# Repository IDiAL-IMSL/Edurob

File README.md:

# EduRobV2
[Homepage](https://www.imsl.fh-dortmund.de/mobile-roboter/edurob/)
## Educational robot with support for various drive kinematics

EduRob is a handy mobile robot specially designed for education. Through clever design, it is possible to cover different types of drives such as Mecanum, Omniwheel, and differential drive.

## Detailed information:

[Getting Started](Doc/README.md)

[Partslist](Doc/Partslist/README.md)

[PCB](https://github.com/IDiAL-IMSL/Edurob-PCB)

[CAD](https://github.com/IDiAL-IMSL/Edurob-CAD/README.md)

## Example projects:

[SLAM](Projects/SLAM/README.md)

[Line Follower](https://github.com/blssed/EduRob-LineFollower)

---

## Background

In the robotics lab, there is a wide range of different robots available for use in teaching and for the completion of thesis projects. However, they all share one major disadvantage: they prefer to drive themselves rather than being carried. As a result, their application is limited to the lab itself and adjacent rooms.

Especially for basic training in mobile robotics such as controlling different types of drives (Mecanum, Omniwheel, or differential drive), implementing control tasks, and connecting sensors, the experimental area of the robotics lab is not necessarily required. This led to the requirement of developing a flexible platform that can cover all types of drives, and small enough to be taken in a backpack to the home office.

# Possible configurations

EduRob can be equipped with three or four motors and different types of wheels. The motors can be flexibly reconnected by loosening two screws, and other wheels can be attached to the motor shaft.

## Mecanum 

With four motors at the four outer corners, EduRob can be turned into a robot with a classic Mecanum drive. The driving behavior is thus similar to that of OmniMan and the other Mecanum robots of the IMSL.

## Omniwheel with three wheels (120°)

With three motors, EduRob can simulate the classic omniwheel configuration. Three wheels rotated by 120° each allow for omnidirectional driving behavior.

## Omniwheel with four wheels (90°)

In addition to the classic arrangement with three omniwheels, EduRob can also simulate the special form with four omniwheels. Here, four omniwheels are arranged with a rotation of 90° to each other. In comparison to the Mecanum arrangement, the wheels are rotated by about 45°. In this configuration, EduRob can also be driven omnidirectionally.

## Differential drive or Skid-Steer drive

The driving behavior of the Pioneer robots in the IMSL inventory is made possible by the use of four wheels. Even though the arrangement of the wheels is similar to the Mecanum arrangement, sideways movement is not possible due to the use of classic wheels without freewheeling rollers. In addition to forward and backward movement and rotation around the center of the platform, driving in circular arcs is possible. This type of drive is also called Skid-Steer drive. Due to the 4x4 drive, this configuration is particularly suitable for rough terrain. The absence of freewheeling rollers on the wheels also means they are less likely to become contaminated or blocked.

By using two classic wheels and one or two non-driven Omniwheels, a proper differential drive is also possible. In this case, the rotation point moves to the midpoint between the two driven wheels. While this affects the robot's turning behavior (the front part swings out), it still maintains its limited range of movement (forward, backward, turning, and driving in circles). However, the "off-road" capability is reduced by the reduction to two driven wheels, and the use of Omniwheels increases the risk of contamination of free-rolling rollers.

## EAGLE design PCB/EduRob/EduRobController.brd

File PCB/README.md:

# EduRobController
[Homepage](https://www.imsl.fh-dortmund.de/mobile-roboter/edurob/)
## EduRob PCB

---

|No.| Device | URL |
|:---:|:---:|:---:|
| 1 |ESP32-PICO-KIT| [Link](https://docs.espressif.com/projects/esp-idf/en/latest/esp32/hw-reference/esp32/get-started-pico-kit.html)  |
| 2 | Dual DC Motordriver TB6612FNG (1A)  | [Link](https://www.sparkfun.com/products/14451)  |
| 3 | Motor 3 connector  | [Link](https://www.reichelt.de/jst-stiftleiste-rm-2-5-mm-1x6-polig-gerade-eh-jst-eh6p-st-p190551.html?search=JST+EH6P+ST+JST)  |
| 4 | Motor 1 connector  | [Link](https://www.reichelt.de/jst-stiftleiste-rm-2-5-mm-1x6-polig-gerade-eh-jst-eh6p-st-p190551.html?search=JST+EH6P+ST+JST)    |
| 5 | Supply Voltage Connector (max. 5VDC)  | -  |
| 6 | 5x20 Fuse (4A)  | -  |
| 7 | Supply Voltage Indicator  | -  |
| 8 | USB Voltage Indicator  | -  |
| 9 | Motor Enable Indicator  | -  |
| 10 | Logic Voltage Indicator  | -  |
| 11 | GPIO Header  | -  |
| 12 | Motor 0 connector  | [Link](https://www.reichelt.de/jst-stiftleiste-rm-2-5-mm-1x6-polig-gerade-eh-jst-eh6p-st-p190551.html?search=JST+EH6P+ST+JST)    |
| 13 | Motor 2 connector  | [Link](https://www.reichelt.de/jst-stiftleiste-rm-2-5-mm-1x6-polig-gerade-eh-jst-eh6p-st-p190551.html?search=JST+EH6P+ST+JST)    |
| 14 | Reset Button  | -    |

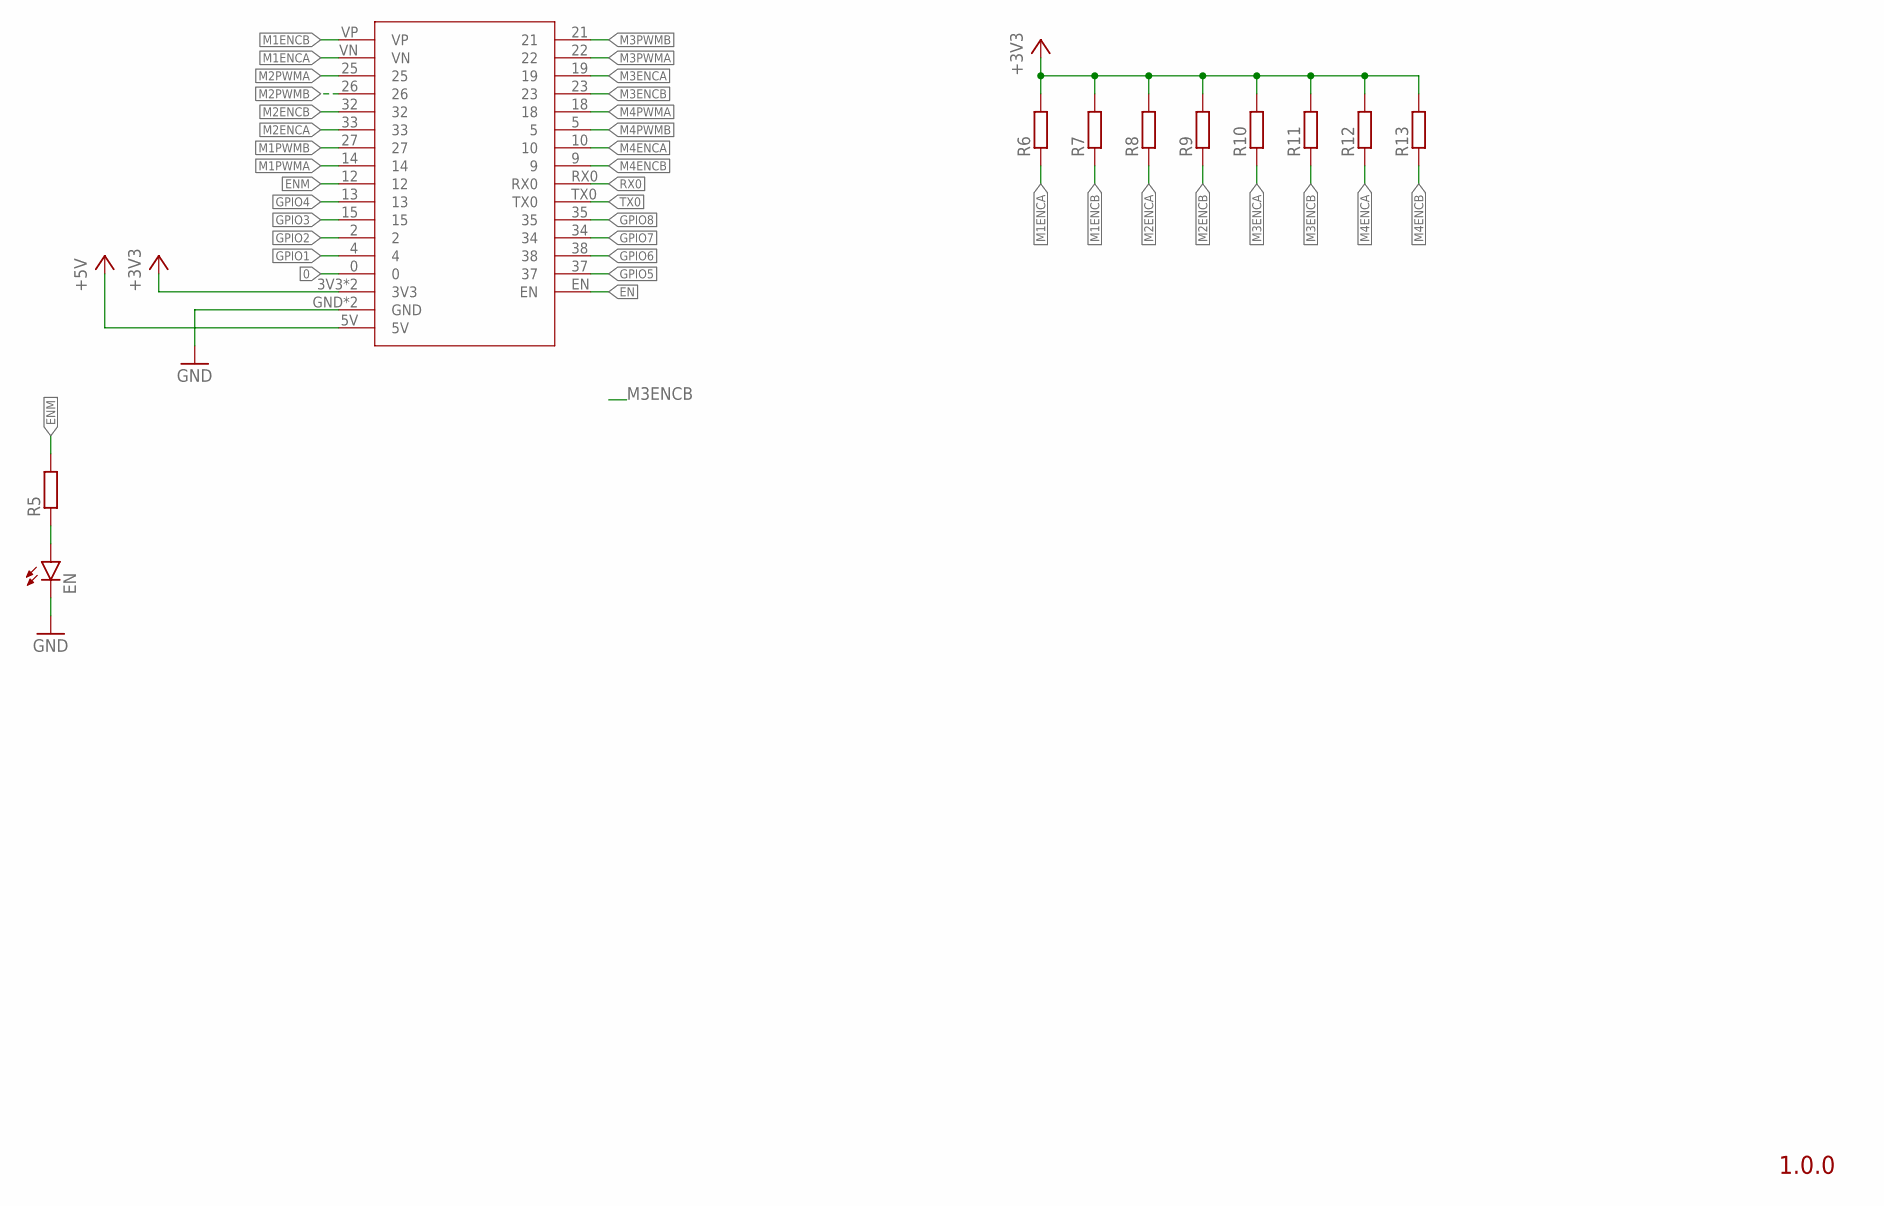
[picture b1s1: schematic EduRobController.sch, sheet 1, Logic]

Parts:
EN: LEDCHIP-LED0805; CHIP-LED0805
R5: R-EU_R0805; R0805
R6, R7, R8, R9, R10, R11, R12, R13: R-EU_R0603; R0603
U$1: ESP32

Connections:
0: U$1.0
+3V3: R6.2, R7.2, R8.2, R9.2, R10.2, R11.2, R12.2, R13.2, U$1.3V3, U$1.3V3. (3V3); also elsewhere on the board
+5V: U$1.5V; also elsewhere on the board
EN: U$1.EN; also elsewhere on the board
ENM: R5.2, U$1.12; also elsewhere on the board
GND: EN.C, U$1.GND, U$1.GND. (GND); also elsewhere on the board
GPIO1: U$1.4; also elsewhere on the board
GPIO2: U$1.2; also elsewhere on the board
GPIO3: U$1.15; also elsewhere on the board
GPIO4: U$1.13; also elsewhere on the board
GPIO5: U$1.37; also elsewhere on the board
GPIO6: U$1.38; also elsewhere on the board
GPIO7: U$1.34; also elsewhere on the board
GPIO8: U$1.35; also elsewhere on the board
M1ENCA: R6.1, U$1.VN; also elsewhere on the board
M1ENCB: R7.1, U$1.VP; also elsewhere on the board
M1PWMA: U$1.14; also elsewhere on the board
M1PWMB: U$1.27; also elsewhere on the board
M2ENCA: R8.1, U$1.33; also elsewhere on the board
M2ENCB: R9.1, U$1.32; also elsewhere on the board
M2PWMA: U$1.25; also elsewhere on the board
M2PWMB: U$1.26; also elsewhere on the board
M3ENCA: R10.1, U$1.19; also elsewhere on the board
M3ENCB: R11.1, U$1.23; also elsewhere on the board
M3PWMA: U$1.22; also elsewhere on the board
M3PWMB: U$1.21; also elsewhere on the board
M4ENCA: R12.1, U$1.10; also elsewhere on the board
M4ENCB: R13.1, U$1.9; also elsewhere on the board
M4PWMA: U$1.18; also elsewhere on the board
M4PWMB: U$1.5; also elsewhere on the board
unnamed: EN.A, R5.1
RX0: U$1.RX0
TX0: U$1.TX0

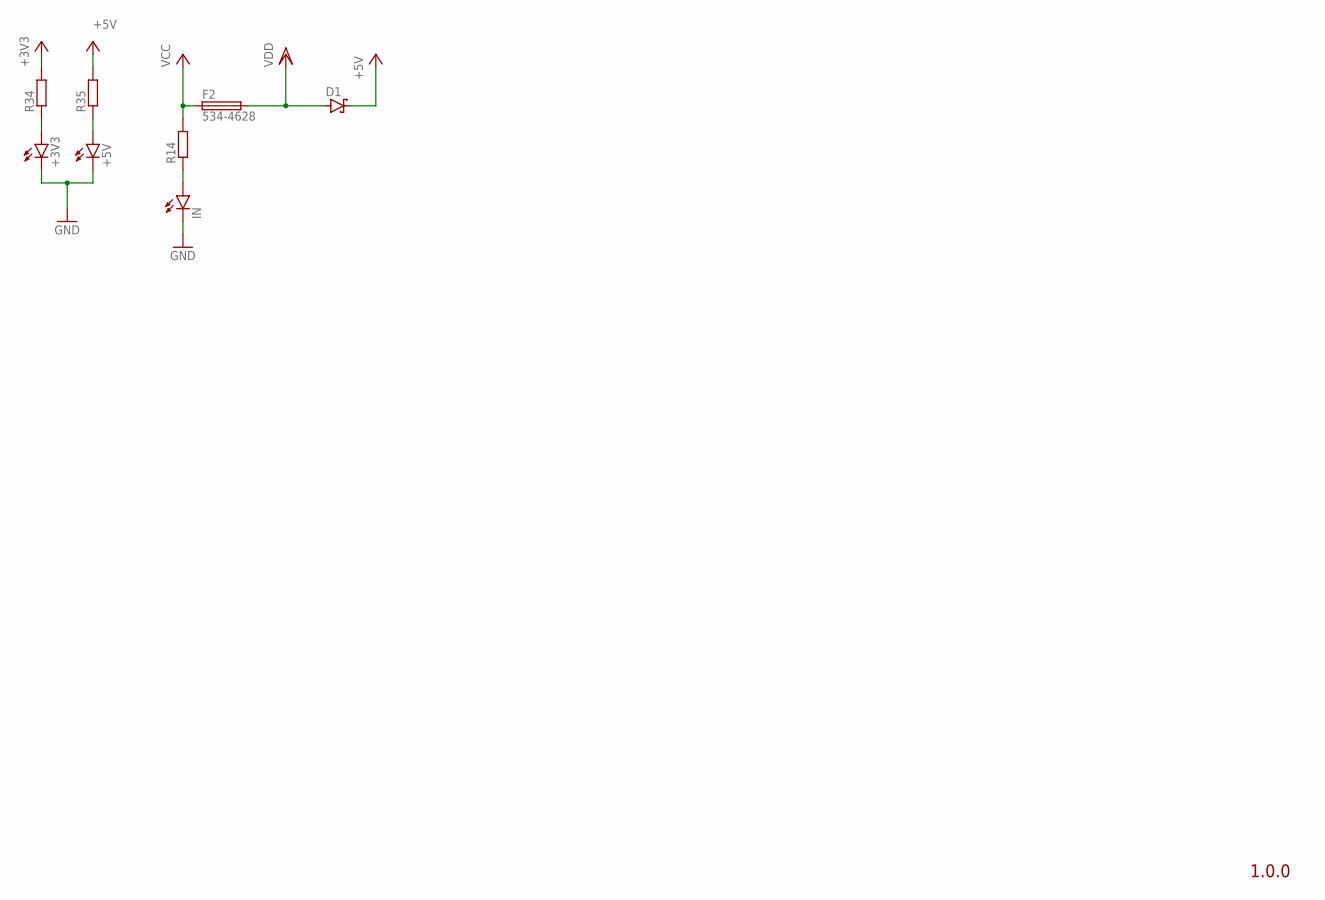
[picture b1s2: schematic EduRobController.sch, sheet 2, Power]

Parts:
+3V3, +5V: LEDCHIP-LED0805; CHIP-LED0805
D1: SCHOTTKY-DIODESMD; SMB
F2: 534-4628; SH22,5
IN: LEDCHIP-LED0805; CHIP-LED0805
R14, R34, R35: R-EU_R0805; R0805

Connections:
+3V3: R34.2; also elsewhere on the board
+5V: D1.C, R35.2; also elsewhere on the board
GND: +3V3.C, +5V.C, IN.C; also elsewhere on the board
unnamed: +3V3.A, R34.1
unnamed: +5V.A, R35.1
unnamed: IN.A, R14.1
VCC: F2.1, R14.2; also elsewhere on the board
VDD: D1.A, F2.2; also elsewhere on the board

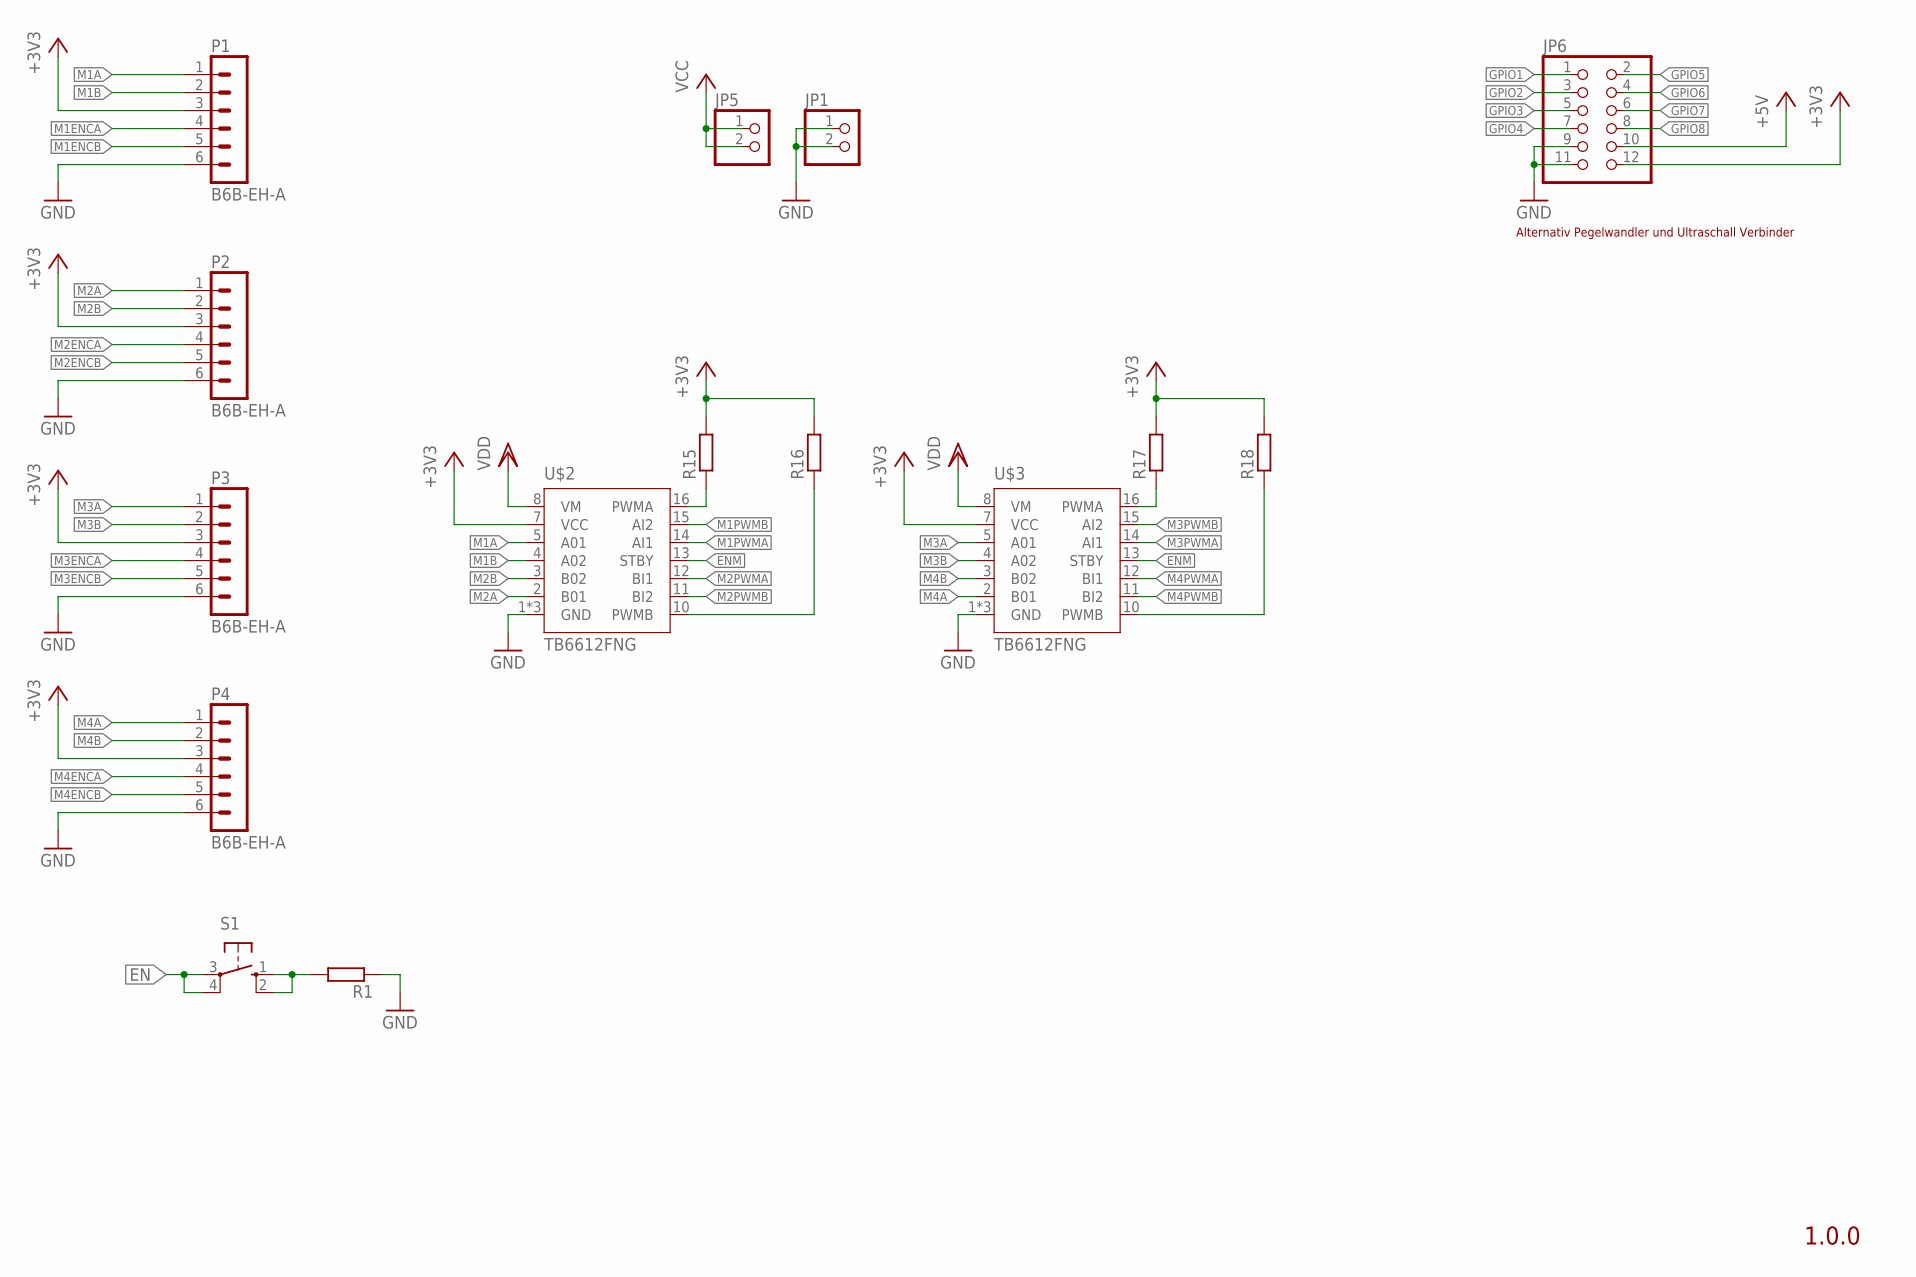
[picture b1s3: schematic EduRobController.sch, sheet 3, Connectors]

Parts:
JP1, JP5: PINHD-1X2; 1X02
JP6: PINHD-2X6; 2X06
P1, P2, P3, P4: B6B-EH-A
R1, R15, R16, R17, R18: R-EU_R0603; R0603
S1: 10-XX; B3F-10XX
U$2, U$3: TB6612FNG; 2X08

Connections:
+3V3: JP6.12, P1.3, P2.3, P3.3, P4.3, R15.2, R16.2, R17.2, R18.2, U$2.7 (VCC), U$3.7 (VCC); also elsewhere on the board
+5V: JP6.10; also elsewhere on the board
EN: S1.3, S1.4 (P1); also elsewhere on the board
ENM: U$2.13 (STBY), U$3.13 (STBY); also elsewhere on the board
GND: JP1.1, JP1.2, JP6.9, JP6.11, P1.6, P2.6, P3.6, P4.6, R1.1, U$2.1 (GND), U$2.6 (GND), U$2.9 (GND), U$3.1 (GND), U$3.6 (GND), U$3.9 (GND); also elsewhere on the board
GPIO1: JP6.1; also elsewhere on the board
GPIO2: JP6.3; also elsewhere on the board
GPIO3: JP6.5; also elsewhere on the board
GPIO4: JP6.7; also elsewhere on the board
GPIO5: JP6.2; also elsewhere on the board
GPIO6: JP6.4; also elsewhere on the board
GPIO7: JP6.6; also elsewhere on the board
GPIO8: JP6.8; also elsewhere on the board
M1A: P1.1, U$2.5 (A01)
M1B: P1.2, U$2.4 (A02)
M1ENCA: P1.4; also elsewhere on the board
M1ENCB: P1.5; also elsewhere on the board
M1PWMA: U$2.14 (AI1); also elsewhere on the board
M1PWMB: U$2.15 (AI2); also elsewhere on the board
M2A: P2.1, U$2.2 (B01)
M2B: P2.2, U$2.3 (B02)
M2ENCA: P2.4; also elsewhere on the board
M2ENCB: P2.5; also elsewhere on the board
M2PWMA: U$2.12 (BI1); also elsewhere on the board
M2PWMB: U$2.11 (BI2); also elsewhere on the board
M3A: P3.1, U$3.5 (A01)
M3B: P3.2, U$3.4 (A02)
M3ENCA: P3.4; also elsewhere on the board
M3ENCB: P3.5; also elsewhere on the board
M3PWMA: U$3.14 (AI1); also elsewhere on the board
M3PWMB: U$3.15 (AI2); also elsewhere on the board
M4A: P4.1, U$3.2 (B01)
M4B: P4.2, U$3.3 (B02)
M4ENCA: P4.4; also elsewhere on the board
M4ENCB: P4.5; also elsewhere on the board
M4PWMA: U$3.12 (BI1); also elsewhere on the board
M4PWMB: U$3.11 (BI2); also elsewhere on the board
unnamed: R1.2, S1.1 (S), S1.2 (S1)
unnamed: R17.1, U$3.16 (PWMA)
unnamed: R18.1, U$3.10 (PWMB)
unnamed: R15.1, U$2.16 (PWMA)
unnamed: R16.1, U$2.10 (PWMB)
VCC: JP5.1, JP5.2; also elsewhere on the board
VDD: U$2.8 (VM), U$3.8 (VM); also elsewhere on the board

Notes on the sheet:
Alternativ Pegelwandler und Ultraschall Verbinder

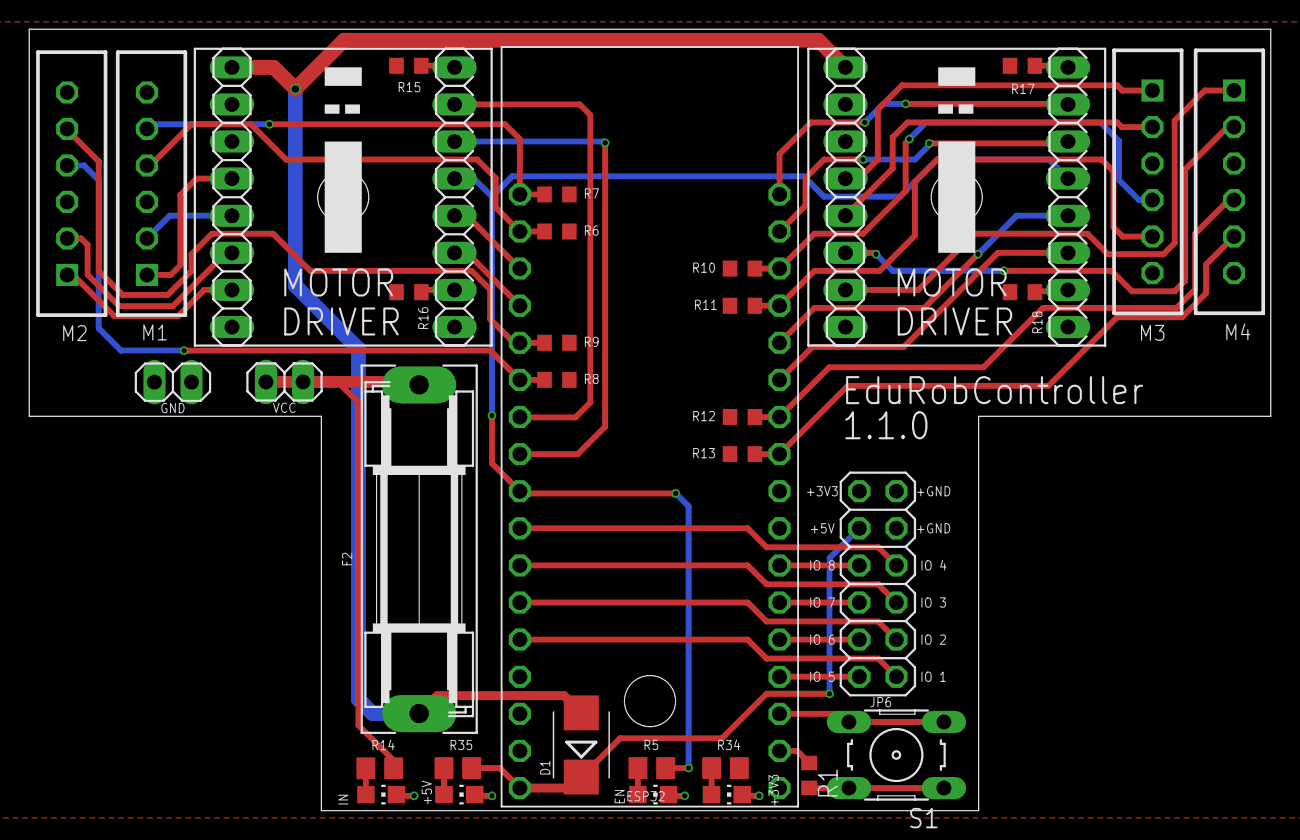
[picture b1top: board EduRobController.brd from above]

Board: 2 copper layers, 85.0 x 53.5 mm, 34 parts (0 on the bottom side), 48 nets.

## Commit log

2023-03-20 Initial upload
2023-03-21 Added links to detailed infos
2023-03-21 Added more infos
2023-03-21 Fixed CAD link
2023-03-21 Add EduRobController
2023-03-21 Removed entry
2023-04-27 Added instructions
2023-04-27 Fix typo
2023-07-31 Added Serial-Interface for ROS
2023-07-31 Added Projects "Line Follower" and "SLAM"
2023-08-02 Updated microros-Library, added custom message
2023-08-02 added staticTFs
2023-08-23 Added TF and custom speed msg
2023-11-23 New Connectors and minor changes
2023-12-14 Fixed movement bug
2024-01-29 Removed custom speed message
2024-01-30 Updated dimensions
2024-01-30 Added missing components
2024-05-14 Moved kinematics matrices, added ability to have multiple dimensions for different kinematics, added new Rad2PWM calculation of maximum revolutions, changed min max of PID to avoid overshoot, fixed s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
2024-07-30 Updated Software to EdurobV2 and Changed development environment to PlatformIO
2024-10-15 Added ROS 1 Noetic
2025-06-11 Removed unnecessary code to test pwm
2025-09-23 New Webserver
    New Webserver Implementation
    This branch introduces a new webserver implementation with the following enhancements:
    Configurable Kinematik – Kinematik settings can now be configured per webserver instance.
    Math Expression Evaluation – Support added for evaluating mathematical expressions.
    Interpolator Settings Preservation – Interpolator configurations are now preserved during page reloads, as long as the webserver remains running.
    Improved Asset Handling – HTML and CSS are now stored as .html and .css files, which are then converted using tostring.py into .cpp and .h files.
2025-10-02 Added ROS2 Jazzy support, moved from PlatformIO to Arduino for compatibility
2025-10-02 Added ROS2 Library
2025-10-08 Fix spelling of header file of Arduino library
2025-10-14 Improve odometry updates by using increments
    Directly use the encoder's increments to update the EduRob's odometry state
    without calculating speeds first. This removes timer jitter that would
    interfere with the odometry calculation.
    Rational: Since the increments directly state the wheel's rotations and thereby
    through the inverse kinematics the change in the robot's position there is no
    benefit in first calculating wheel speeds to later use the wheel speed to get
2025-10-14 Do not filter acceleration for cmd_vel
    Since EduRob can not make any assumptions on the source of the /cmd_vel
    messages filtering them removes the ability to quickly stop the robot or do any
    other velocity changes. The velocities are better filtered by the node creating
    the /cmd_vel messages.
2025-10-14 Remove a duplicated code line and add block
2025-10-17 Update the parameters to EduRob V2
2025-10-17 Fix Mecanum transform matrices
2025-10-29 Update README.md
    Updates the README with a Quickstart on how to use the Edurob V2 with ROS2 Jazzy (via micro_ros_agent) or only with the included Arduino Sketch.
2025-11-02 Bug Fixes & QOL
    Fix: URL parser now works
    QOL: Added Reset & Standard Kinematics URL
    Chore: Cleaned up Web Frontend
    Bug: EigenMatrix mismatch in .ino (line 89)
2025-11-03 Bug Fix & Chores
    Fix: Compiler Error
    Chore: Cleaned up Web Frontend
2025-11-10 Add LIDAR mount v6 step file for Edurob V2
2025-11-16 Fix ROS_EN
    Fix ROS_EN and make project compilable when ROS_EN is not defined.
2025-11-16 Add serial transport to micro ros
    Add option to use uart0 for transporting micro ros messages.
2025-11-17 Make mainsite link to kinematic sites dynamic; remove intermediate info page
    Replaced static link with dynamic routing to kinematic sites
    Added multiple layout variations for testing which performs better
2025-11-19 WIP: Saved-state feedback prototype (Mecanum test bed)
    This PR adds an initial prototype of saved-state feedback for form inputs.
    The Mecanum configuration page is currently used as a test bed to verify the
    logic and UI behavior.
    Included:
    - live detection of differences between form values and URL params
    - numeric normalization (0, 0.0, 0.00 → equal)
2025-11-23 WIP: Saved-state feedback prototype (Mecanum test bed)
    This PR extends the saved-state feedback prototype by adding a dedicated
    "loaded" state for situations where the configuration page is opened
    without URL parameters.
    Included:
    - introduce 'loaded' state when URL param set is empty
    - refine saved/unsaved check logic
2025-11-30 Created gyroscope driver
2026-03-19 Remove EduRob V1 PCB and reference PCB repro
2026-03-19 Make link to PCB repro absolute
2026-03-19 Move CAD to own repro

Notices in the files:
parts and their libraries:
con-jst-eh: Copyright (C) 2016, Bob Starr
